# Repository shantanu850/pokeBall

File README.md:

# pokeBall
convertible small size robot
If you find anything missing inform me

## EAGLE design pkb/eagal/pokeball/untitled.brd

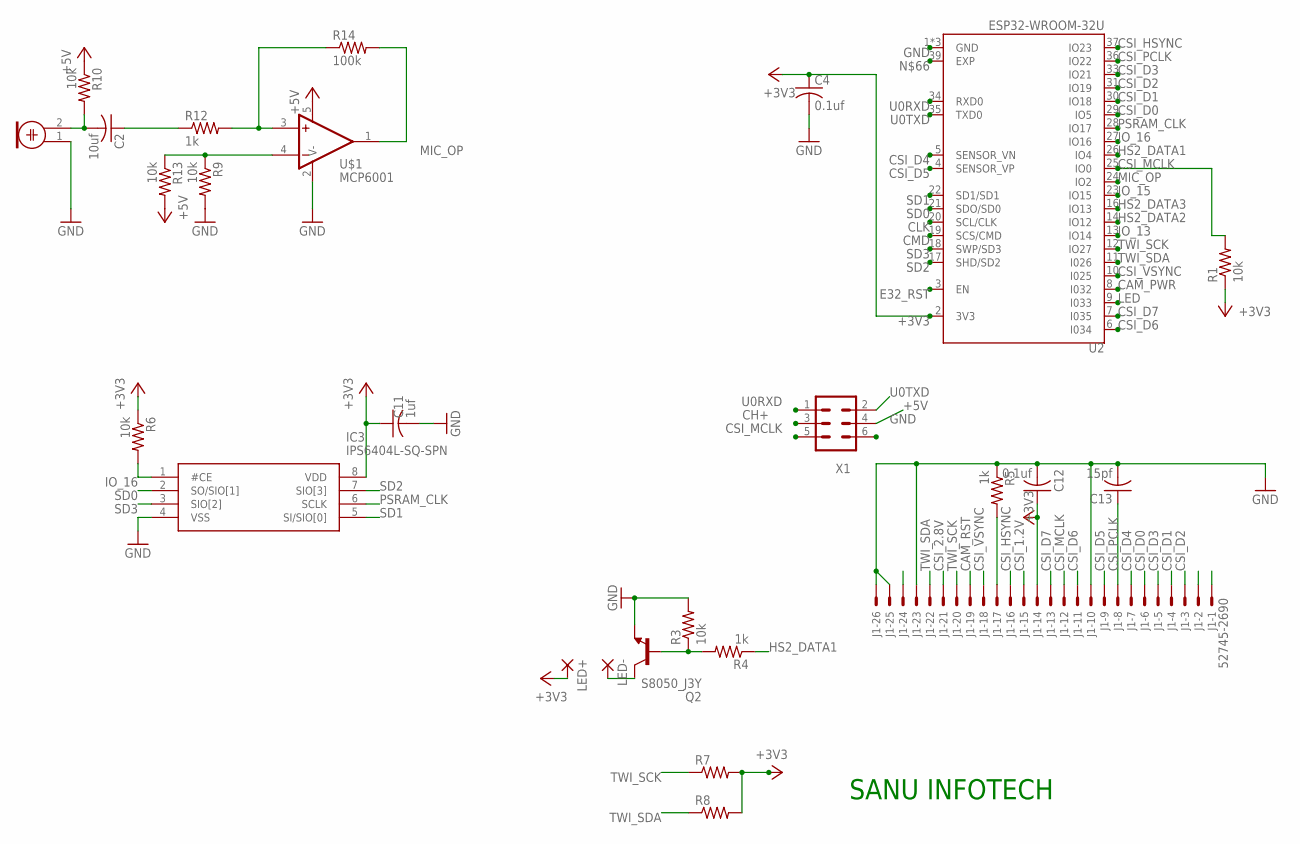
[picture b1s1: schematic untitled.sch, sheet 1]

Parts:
C2: 10uf; C0805
C4, C12: 0.1uf; C0805
C11: 1uf; C0805
C13: 15pf; C0805
IC3: IPS6404L-SQ-SPN; SOIC127P600X175-8N
J1: 52745-2690
LED+: SMD2; SMD1,27-2,54
LED-: SMD2; SMD1,27-2,54
M1: ELECTRET_MICROPHON-F6035AP; F6035AP
Q2: S8050_J3Y; SOT23
R1, R3, R6, R9, R10, R13: 10k; R0805
R4, R5, R12: 1k; R0805
R7, R8: R-US_R0805; R0805
R14: 100k; R0805
U2: ESP32-WROOM-32U; XCVR_ESP32-WROOM-32U
U$1: MCP6001; SOT23-5
X1: MA03-2

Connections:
+3V3: C4.1, C11.1, C12.1, IC3.8 (VDD), J1.14, LED+.1, R1.1, R6.1, R7.2, R8.2, U2.2 (3V3); also elsewhere on the board
+5V: R10.1, R13.2, U$1.5 (V+), X1.4; also elsewhere on the board
CAM_PWR: U2.8 (I032); also elsewhere on the board
CAM_RST: J1.19
CH+: X1.3; also elsewhere on the board
CLK: U2.20 (SCL/CLK)
CMD: U2.19 (SCS/CMD)
CSI_1.2V: J1.15; also elsewhere on the board
CSI_2.8V: J1.21; also elsewhere on the board
CSI_D0: J1.6, U2.29 (IO5)
CSI_D1: J1.4, U2.30 (IO18)
CSI_D2: J1.3, U2.31 (IO19)
CSI_D3: J1.5, U2.33 (IO21)
CSI_D4: J1.7, U2.5 (SENSOR_VN)
CSI_D5: J1.9, U2.4 (SENSOR_VP)
CSI_D6: J1.11, U2.6 (I034)
CSI_D7: J1.13, U2.7 (I035)
CSI_HSYNC: J1.16, U2.37 (IO23)
CSI_MCLK: J1.12, R1.2, U2.25 (IO0), X1.5
CSI_PCLK: C13.1, J1.8, U2.36 (IO22)
CSI_VSYNC: J1.18, U2.10 (I025)
E32_RST: U2.3 (EN)
GND: C4.2, C11.2, C12.2, C13.2, IC3.4 (VSS), J1.10, J1.23, J1.25, J1.26, M1.1, Q2.2 (E), R3.2, R5.1, R9.2, U2.1 (GND), U2.15 (GND), U2.38 (GND), U$1.2 (V-), X1.6; also elsewhere on the board
HS2_DATA1: R4.1, U2.26 (IO4)
HS2_DATA2: U2.14 (IO12); also elsewhere on the board
HS2_DATA3: U2.16 (IO13); also elsewhere on the board
IO_13: U2.13 (IO14)
IO_15: U2.23 (IO15)
IO_16: IC3.1 (#CE), R6.2, U2.27 (IO16)
LED: U2.9 (I033)
MIC_OP: R14.2, U2.24 (IO2), U$1.1 (OUT)
unnamed: Q2.1 (B), R3.1, R4.2
unnamed: LED-.1, Q2.3 (C)
unnamed: J1.17, R5.2
unnamed: C2.2, M1.2, R10.2
unnamed: C2.1, R12.1
unnamed: R12.2, R14.1, U$1.3 (+IN)
unnamed: R9.1, R13.1, U$1.4 (-IN)
PSRAM_CLK: IC3.6 (SCLK), U2.28 (IO17)
SD0: IC3.2 (SO/SIO[1]), U2.21 (SDO/SD0)
SD1: IC3.5 (SI/SIO[0]), U2.22 (SD1/SD1)
SD2: IC3.7 (SIO[3]), U2.17 (SHD/SD2)
SD3: IC3.3 (SIO[2]), U2.18 (SWP/SD3)
TWI_SCK: J1.20, R7.1, U2.12 (IO27)
TWI_SDA: J1.22, R8.1, U2.11 (I026)
U0RXD: U2.34 (RXD0), X1.1
U0TXD: U2.35 (TXD0), X1.2

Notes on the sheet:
SANU INFOTECH

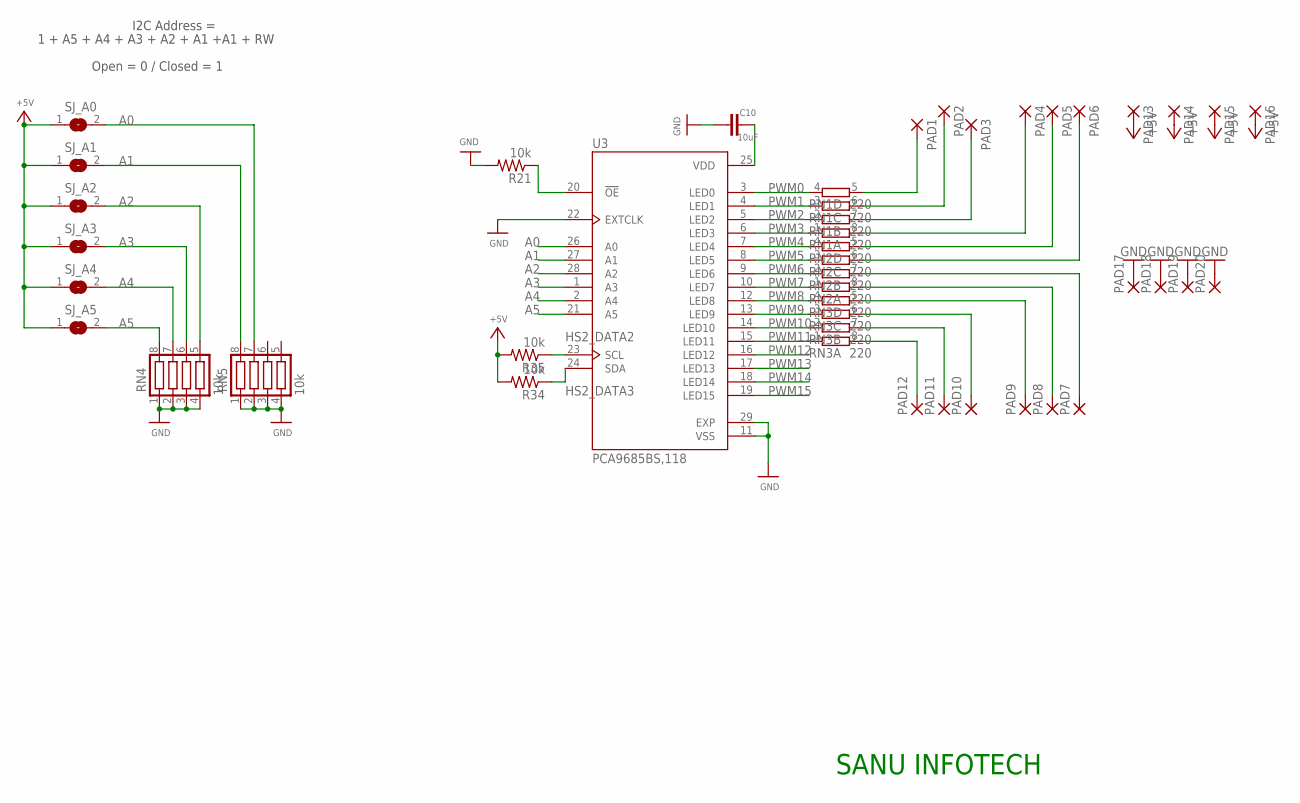
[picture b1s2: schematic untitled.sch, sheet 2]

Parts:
C10: 10uF; C0805
PAD1, PAD2, PAD3, PAD4, PAD5, PAD6, PAD7, PAD8, PAD9, PAD10, PAD11, PAD12, PAD13, PAD14, PAD15, PAD16, PAD17, PAD18, PAD19, PAD20: 1,6/0,8
R21, R34, R35: 10k; R0805
RN1, RN2, RN3: 220; 0603-ARV
RN4, RN5: 10k; CTS742C083
SJ_A0, SJ_A1, SJ_A2, SJ_A3, SJ_A4, SJ_A5: SJ
U3: PCA9685BS,118; QFN65P600X600X100-29N

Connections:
+5V: PAD13.1, PAD14.1, PAD15.1, PAD16.1, R34.2, R35.2, SJ_A0.1, SJ_A1.1, SJ_A2.1, SJ_A3.1, SJ_A4.1, SJ_A5.1; also elsewhere on the board
A0: RN5.7, SJ_A0.2, U3.26 (A0)
A1: RN5.8, SJ_A1.2, U3.27 (A1)
A2: RN4.5, SJ_A2.2, U3.28 (A2)
A3: RN4.6, SJ_A3.2, U3.1 (A3)
A4: RN4.7, SJ_A4.2, U3.2 (A4)
A5: RN4.8, SJ_A5.2, U3.21 (A5)
GND: C10.2, PAD17.1, PAD18.1, PAD19.1, PAD20.1, R21.2, RN4.1, RN4.2, RN4.3, RN4.4, U3.11 (VSS), U3.22 (EXTCLK), U3.29 (EXP); also elsewhere on the board
HS2_DATA2: R35.1, U3.23 (SCL); also elsewhere on the board
HS2_DATA3: R34.1, U3.24 (SDA); also elsewhere on the board
unnamed: PAD1.1, RN1.5 (2)
unnamed: PAD2.1, RN1.6 (2)
unnamed: PAD3.1, RN1.7 (2)
unnamed: PAD4.1, RN1.8 (2)
unnamed: PAD5.1, RN2.5 (2)
unnamed: PAD6.1, RN2.6 (2)
unnamed: PAD7.1, RN2.7 (2)
unnamed: PAD8.1, RN2.8 (2)
unnamed: PAD9.1, RN3.5 (2)
unnamed: PAD10.1, RN3.6 (2)
unnamed: PAD11.1, RN3.7 (2)
unnamed: PAD12.1, RN3.8 (2)
unnamed: RN5.1, RN5.2, RN5.3, RN5.4
unnamed: C10.1, U3.25 (VDD)
OE: R21.1, U3.20 (!OE)
PWM0: RN1.4 (1), U3.3 (LED0)
PWM1: RN1.3 (1), U3.4 (LED1)
PWM2: RN1.2 (1), U3.5 (LED2)
PWM3: RN1.1, U3.6 (LED3)
PWM4: RN2.4 (1), U3.7 (LED4)
PWM5: RN2.3 (1), U3.8 (LED5)
PWM6: RN2.2 (1), U3.9 (LED6)
PWM7: RN2.1, U3.10 (LED7)
PWM8: RN3.4 (1), U3.12 (LED8)
PWM9: RN3.3 (1), U3.13 (LED9)
PWM10: RN3.2 (1), U3.14 (LED10)
PWM11: RN3.1, U3.15 (LED11)
PWM12: U3.16 (LED12)
PWM13: U3.17 (LED13)
PWM14: U3.18 (LED14)
PWM15: U3.19 (LED15)

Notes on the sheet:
1 + A5 + A4 + A3 + A2 + A1 +A1 + RW
I2C Address =
Open = 0 / Closed = 1
SANU INFOTECH

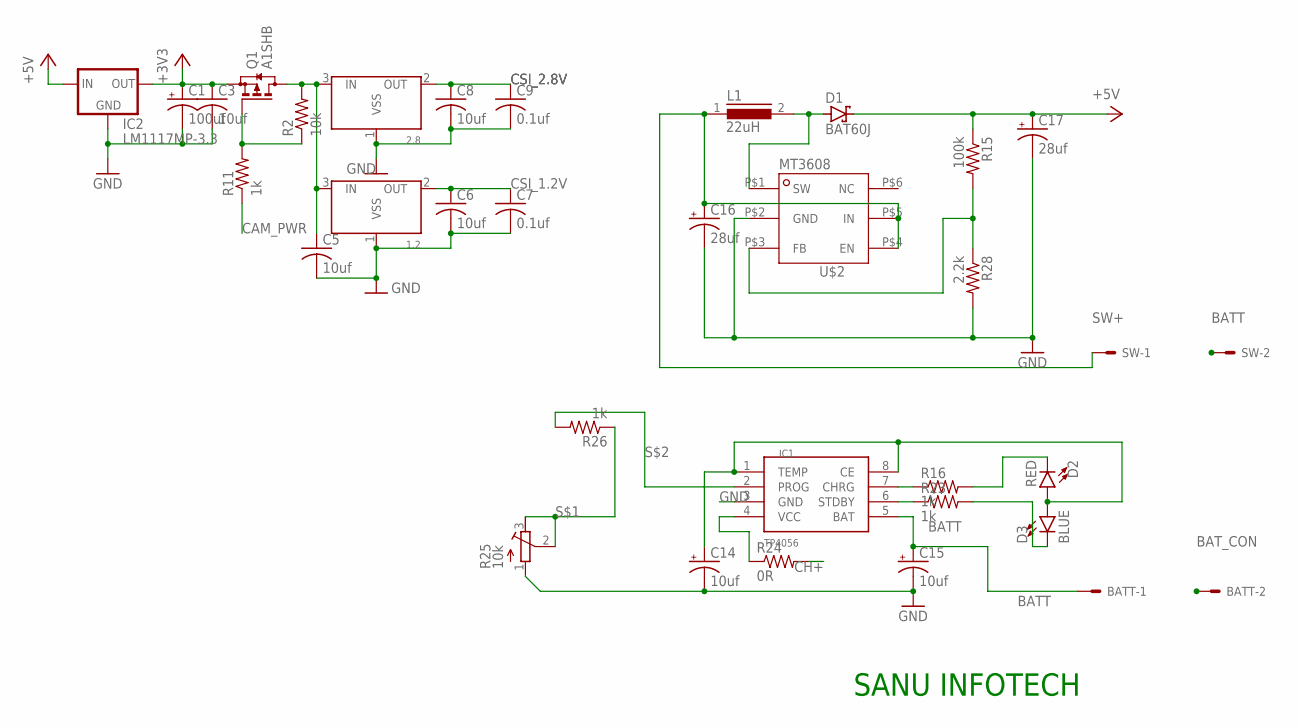
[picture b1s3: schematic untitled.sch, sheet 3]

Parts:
1.2, 2.8: XC6206SOT-23; XC6206_SOT-23
BATT: 332-02
C1: 100uf; B/3528-21R
C3, C5, C6, C8: 10uf; C0805
C7, C9: 0.1uf; C0805
C14, C15: 10uf; B/3528-21W
C16, C17: 28uf; 153CLV-0405
D1: BAT60J; SOD323_ST
D2: RED; LED-0603
D3: BLUE; LED-0603
IC1: TP4056; SOP-8
IC2: LM1117MP-3.3; SOT223
L1: 22uH; DR74
Q1: A1SHB; SOT23
R2: 10k; R0805
R11: 1k; R0805
R15: 100k; M0805
R16, R23, R26: 1k; M0805
R24: 0R; M0805
R25: 10k; RTRIM4G/J
R28: 2.2k; M0805
SW: 332-02
U$2: MT3608SOT23-6; SOT23-6

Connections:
+3V3: C1.+, C3.1, IC2.2 (OUT), IC2.4 (OUT), Q1.2 (S); also elsewhere on the board
+5V: C17.+, D1.C, IC2.3 (IN), R15.1; also elsewhere on the board
BATT: BATT.1, C15.+, IC1.5 (BAT), SW.2
BAT_CON: BATT.2
CAM_PWR: R11.1; also elsewhere on the board
CH+: R24.2; also elsewhere on the board
CSI_1.2V: 1.2.2 (OUT), C6.1, C7.1; also elsewhere on the board
CSI_2.8V: 2.8.2 (OUT), C8.1, C9.1; also elsewhere on the board
GND: 1.2.1 (VSS), 2.8.1 (VSS), C1.-, C3.2, C5.2, C6.2, C7.2, C8.2, C9.2, C14.-, C15.-, C16.-, C17.-, IC1.3 (GND), IC2.1 (GND), R25.1 (A), R28.2, U$2.P$2 (GND); also elsewhere on the board
unnamed: 1.2.3 (IN), 2.8.3 (IN), C5.1, Q1.3 (D), R2.2
unnamed: Q1.1 (G), R2.1, R11.2
unnamed: C14.+, D2.A, D3.A, IC1.1 (TEMP), IC1.8 (CE)
unnamed: R15.2, R28.1, U$2.P$3 (FB)
unnamed: D2.C, R16.2
unnamed: IC1.4 (VCC), R24.1
unnamed: IC1.6 (STDBY), R23.1
unnamed: IC1.7 (CHRG), R16.1
unnamed: D3.C, R23.2
unnamed: D1.A, L1.2, U$2.P$1 (SW)
S$1: R25.2 (S), R25.3 (E), R26.1
S$2: IC1.2 (PROG), R26.2
SW+: C16.+, L1.1, SW.1, U$2.P$4 (EN), U$2.P$5 (IN)

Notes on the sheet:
SANU INFOTECH

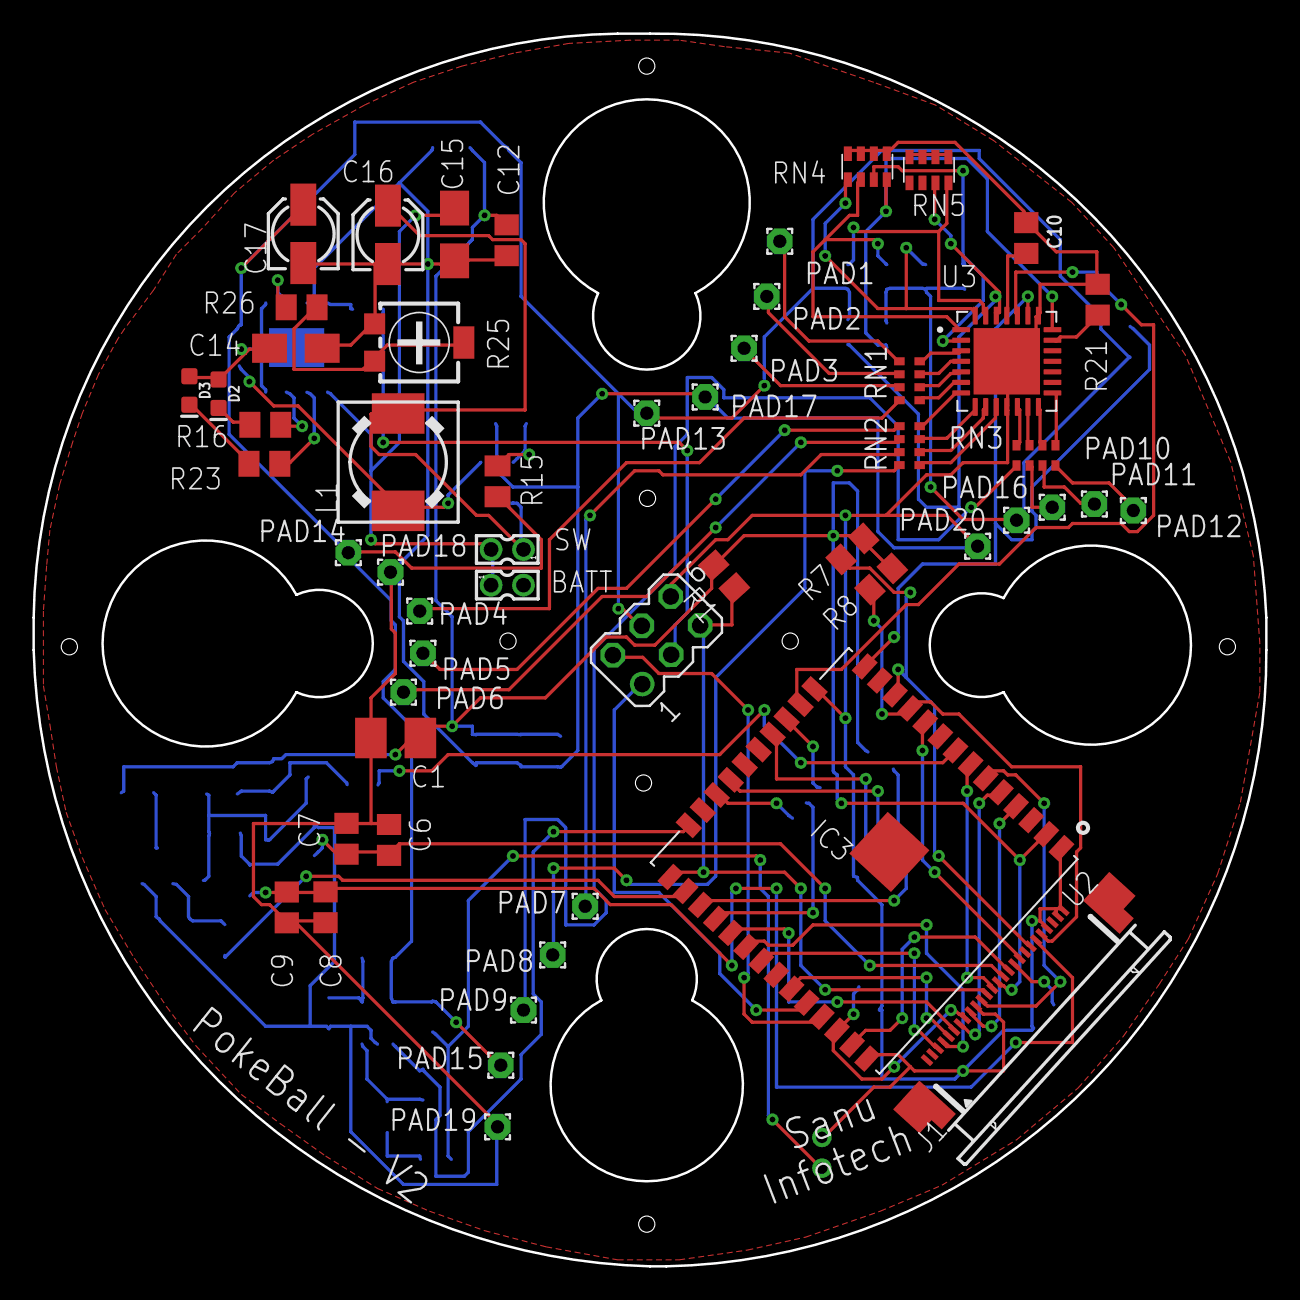
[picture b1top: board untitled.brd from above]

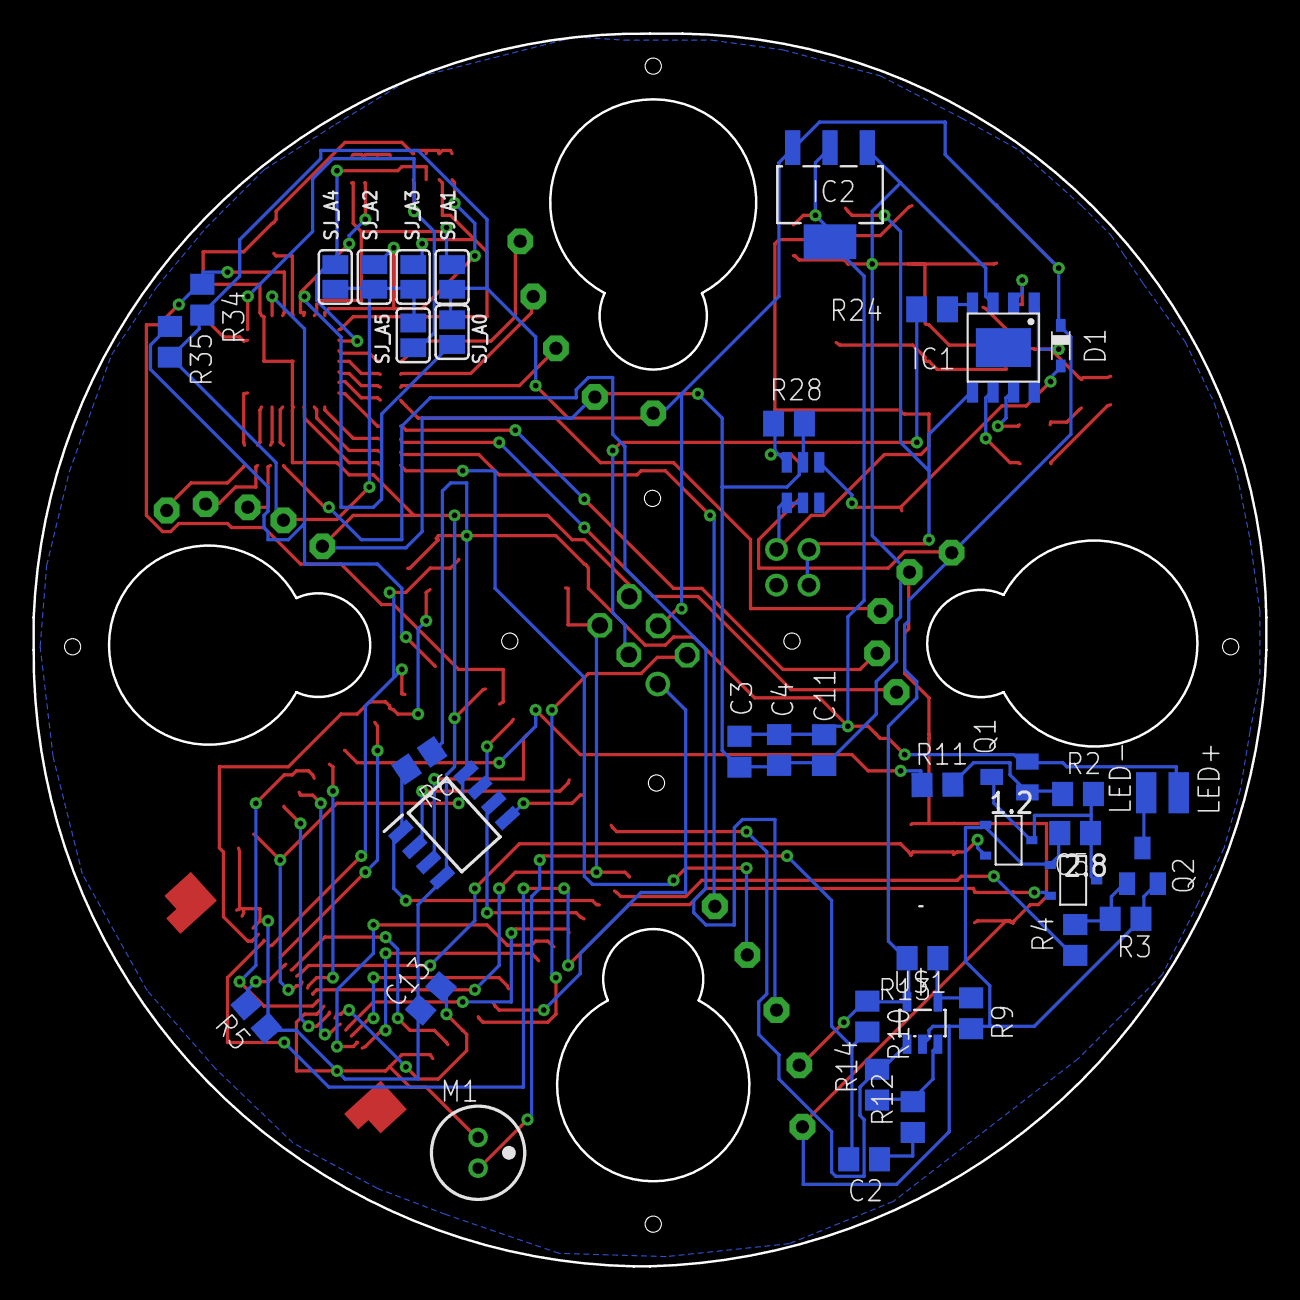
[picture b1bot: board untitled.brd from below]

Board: 2 copper layers, 76.0 x 76.0 mm, 94 parts (40 on the bottom side), 87 nets.

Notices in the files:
parts and their libraries:
SparkFun-LED: Licensing: Creative Commons ShareAlike 4.0 International - https://creativecommons.org/licenses/by-sa/4.0
